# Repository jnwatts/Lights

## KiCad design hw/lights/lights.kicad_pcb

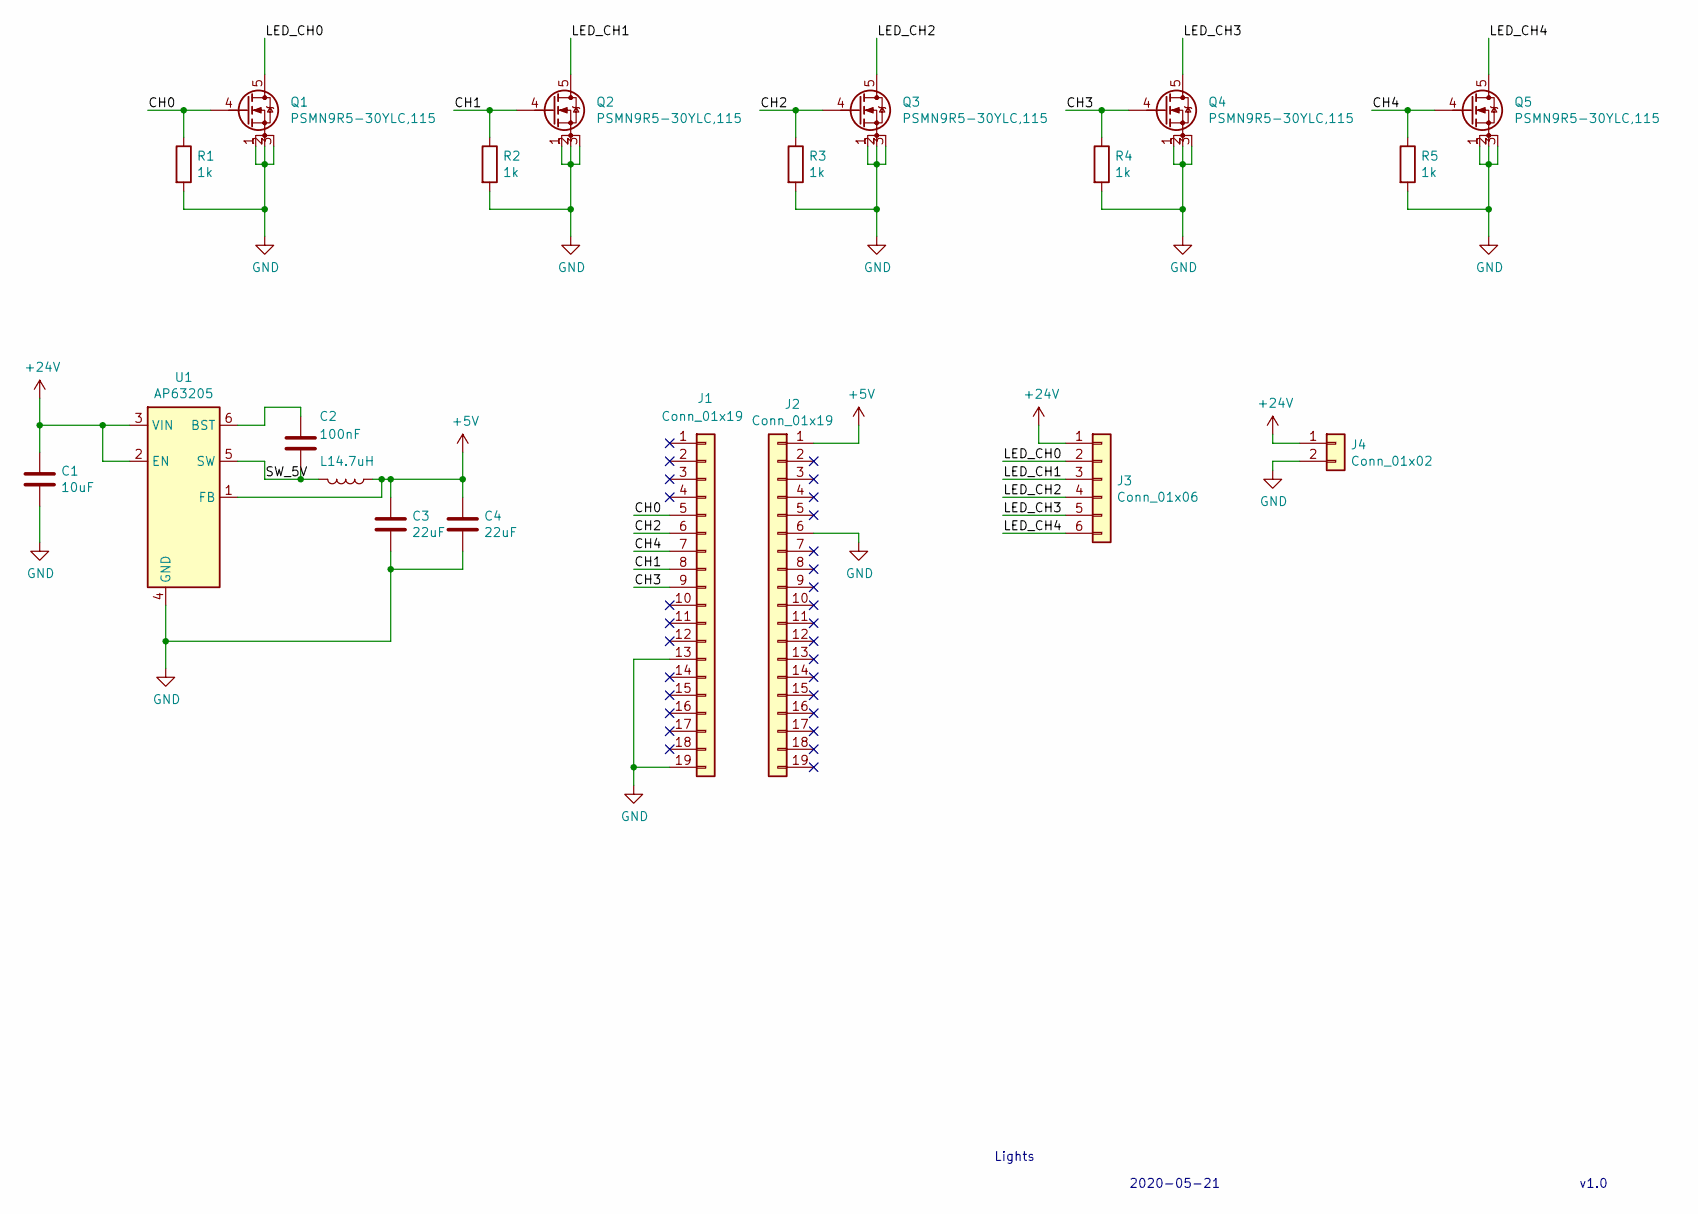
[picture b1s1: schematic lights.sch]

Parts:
C1: 10uF; C_0805_2012Metric_Pad1.15x1.40mm_HandSolder
C2: 100nF; C_0402_1005Metric
C3, C4: 22uF; C_0805_2012Metric_Pad1.15x1.40mm_HandSolder
J1, J2: Conn_01x19; PinSocket_1x19_P2.54mm_Vertical
J3: Conn_01x06; PinSocket_1x06_P2.54mm_Vertical
J4: Conn_01x02; PinSocket_1x02_P2.54mm_Vertical
L1: 4.7uH; L_0805_2012Metric_Pad1.15x1.40mm_HandSolder
Q1, Q2, Q3, Q4, Q5: PSMN9R5-30YLC,115; LFPAK56
R1, R2, R3, R4, R5: 1k; R_0603_1608Metric_Pad1.05x0.95mm_HandSolder
U1: AP63205; TSOT-23-6_HandSoldering

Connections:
+5V: C3.1, C4.1, J2.1, L1.1, U1.1 (FB)
+24V: C1.1, J3.1, J4.1, U1.2 (EN), U1.3 (VIN)
/CH0: J1.5, Q1.4 (G), R1.1
/CH1: J1.8, Q2.4 (G), R2.1
/CH2: J1.6, Q3.4 (G), R3.1
/CH3: J1.9, Q4.4 (G), R4.1
/CH4: J1.7, Q5.4 (G), R5.1
/LED_CH0: J3.2, Q1.5 (D)
/LED_CH1: J3.3, Q2.5 (D)
/LED_CH2: J3.4, Q3.5 (D)
/LED_CH3: J3.5, Q4.5 (D)
/LED_CH4: J3.6, Q5.5 (D)
/SW_5V: C2.2, L1.2, U1.5 (SW)
GND: C1.2, C3.2, C4.2, J1.13, J1.19, J2.6, J4.2, Q1.1 (S), Q1.2 (S), Q1.3 (S), Q2.1 (S), Q2.2 (S), Q2.3 (S), Q3.1 (S), Q3.2 (S), Q3.3 (S), Q4.1 (S), Q4.2 (S), Q4.3 (S), Q5.1 (S), Q5.2 (S), Q5.3 (S), R1.2, R2.2, R3.2, R4.2, R5.2, U1.4 (GND)
unnamed: C2.1, U1.6 (BST)

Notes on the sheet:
v1.0
Lights
2020-05-21

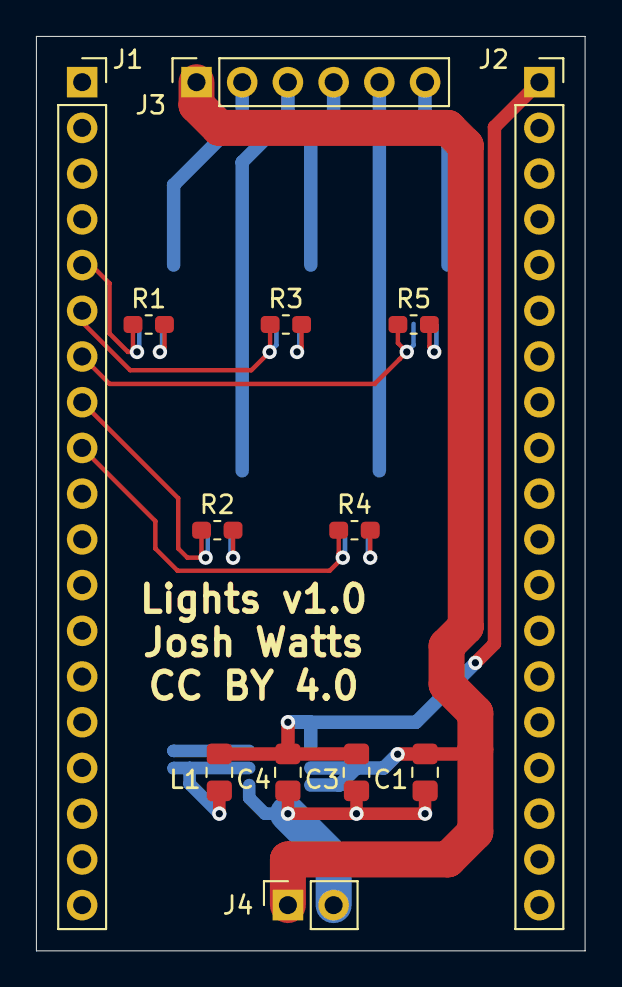
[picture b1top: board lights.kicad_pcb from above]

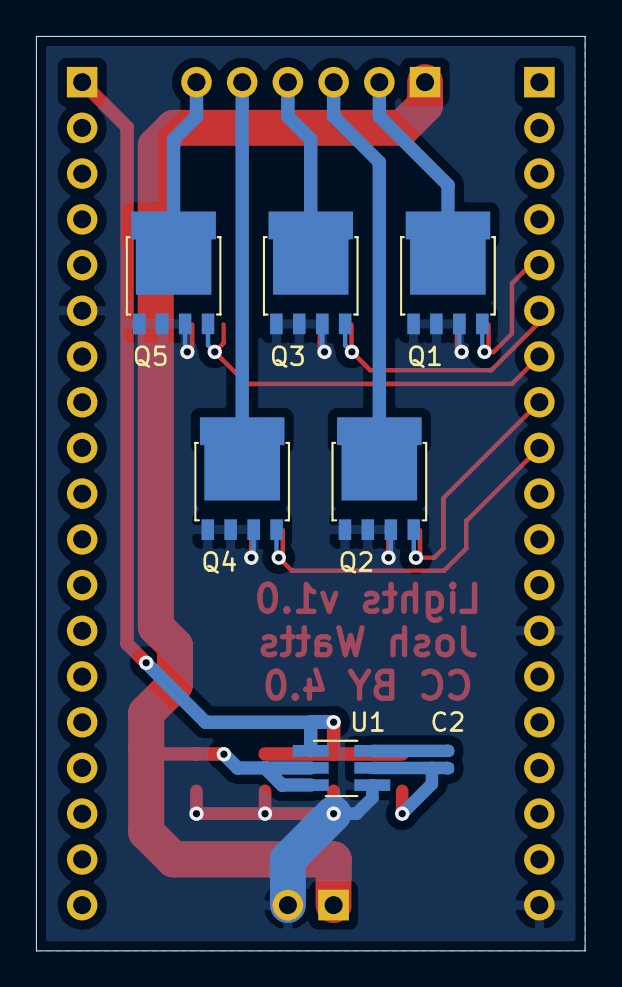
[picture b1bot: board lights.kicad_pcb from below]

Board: 2 copper layers, 30.5 x 50.8 mm, 20 parts (7 on the bottom side), 15 nets.

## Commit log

2020-05-18 Initial commit from working prototype
2020-05-21 First pass at HW - v1.0
2020-06-07 sch: Add channel & IO mapping notes
2020-06-07 lights: Remapped channels to make layout easier
2020-06-07 wifi: Improve error checking
2020-06-07 main: Stack sizes should have been static
2020-06-07 main: Oops, transposed stack size names
2020-09-08 Add web frontend
    This allows for more high-level logic and features without updating HW firmware
2022-06-20 Makefile: Add fullclean to targets
2022-06-20 main: Default to demo mode on startup to indicate liveness
2022-06-20 main: Minimimal delay in lightsFunc()
2022-06-20 wifi: Refactor to support wifi disconnection
2022-06-20 sdkconfig: Minor changes possibly important?
2022-06-20 main: Remove old todo
2022-06-20 Version 1.1

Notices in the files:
hw/lights/lights.kicad_pcb:
CC BY 4.0
